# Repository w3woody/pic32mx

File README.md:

# pic32mx

This is a series of basic projects (including Eagle schematics) for the [PIC32MX270F256B](https://www.microchip.com/wwwproducts/en/PIC32mx270f256b) microcontroller, a 28-pin DIP CPU featuring 256KB of program space and 64KB of RAM. (This makes it an excellent CPU to use in place of the Atmel ATMega processors if you want to write bigger programs and use more memory.)

All these projects are built using the [MPLAB X IDE](https://www.microchip.com/mplab/mplab-x-ide) for the Macintosh, and the [MPLab PICKit 4 In-Circuit Debugger](https://www.microchip.com/Developmenttools/ProductDetails/PG164140).

## VerifyLED

The first project is a very simple one which flashes an LED. This allows you to test to make sure that you can wire up a PIC32 processor correctly and wire an LED to it, and verify your programming tools can connect correctly.

This includes the Eagle files and basic schematic for the simplest circuit necessary to run the PIC32 MPU.

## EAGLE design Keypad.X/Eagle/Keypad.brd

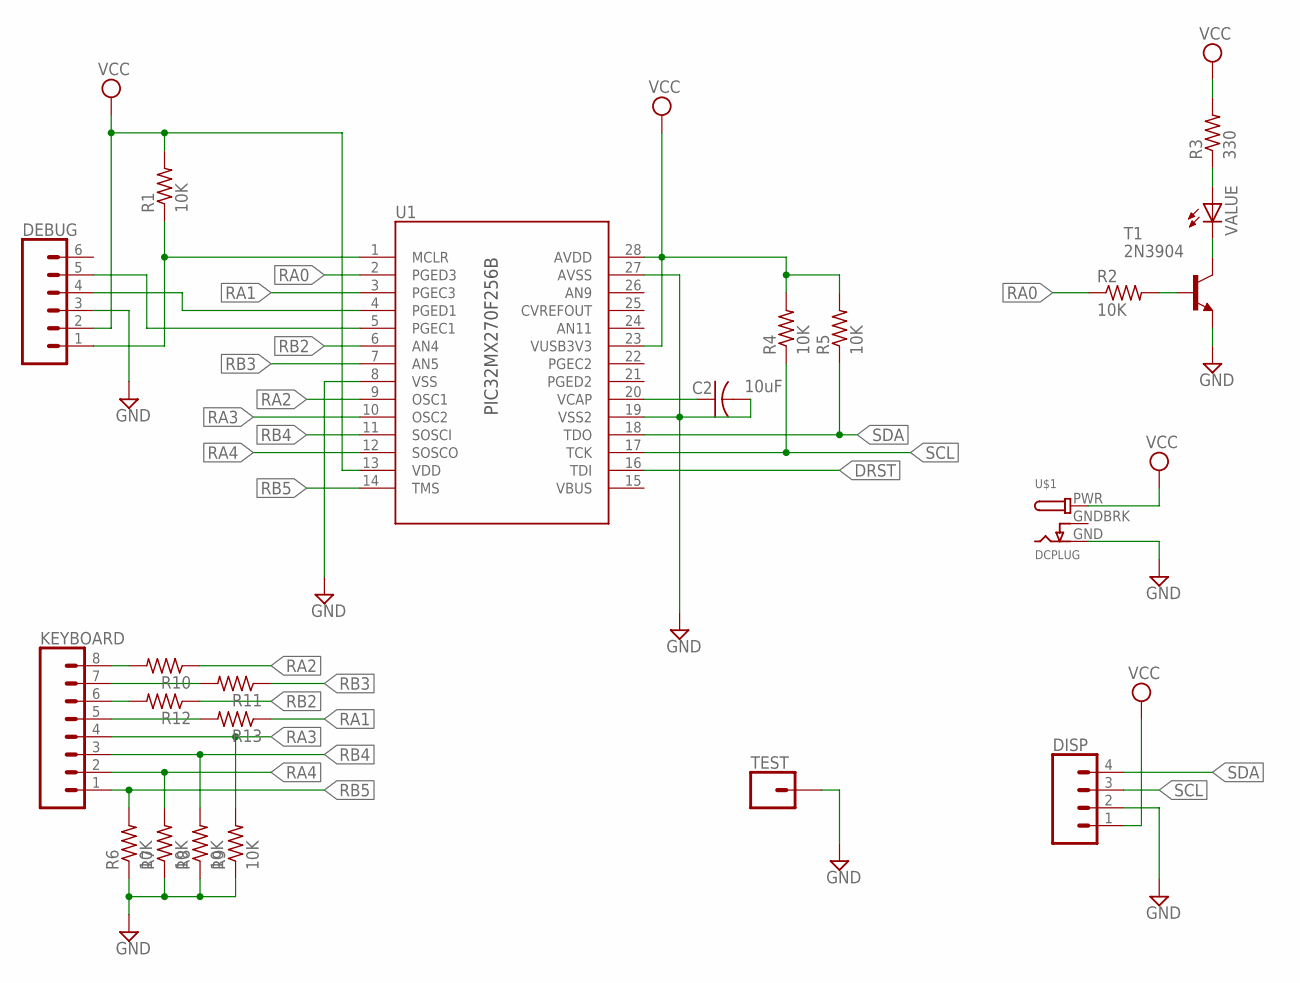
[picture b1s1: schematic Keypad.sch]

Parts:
C2: 10uF; C050-024X044
DEBUG: CONN_06LONGPADS; 1X06_LONGPADS
DISP: CONN_04; 1X04
KEYBOARD: CONN_08"; 1X08
R1, R4, R5, R6, R7, R8, R9: 10K; 0207/10
R2: 10K; 0309/10
R3, R10, R11, R12, R13: 330; 0309/10
T1: 2N3904; TO92
TEST: CONN_01; 1X01
U1: PIC32MX270F256B; DIP28
U$1: DCPLUG; POWER_JACK_SLOT
VALUE: LED5MM

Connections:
DRST: U1.16 (TDI)
GND: C2.2, DEBUG.3, DISP.2, R6.1, R7.1, R8.1, R9.1, T1.3 (E), TEST.1, U1.8 (VSS), U1.19 (VSS2), U1.27 (AVSS), U$1.GND
GNDBREAK: U$1.GNDBRK (GNDBREAK)
unnamed: DEBUG.1, R1.1, U1.1 (MCLR)
unnamed: C2.1, U1.20 (VCAP)
unnamed: KEYBOARD.8, R10.2
unnamed: DEBUG.4, U1.4 (PGED1)
unnamed: DEBUG.5, U1.5 (PGEC1)
unnamed: R2.2, T1.2 (B)
unnamed: T1.1 (C), VALUE.K (C)
unnamed: R3.1, VALUE.A
unnamed: KEYBOARD.7, R11.2
unnamed: KEYBOARD.6, R12.2
unnamed: KEYBOARD.5, R13.2
RA0: R2.1, U1.2 (PGED3)
RA1: R13.1, U1.3 (PGEC3)
RA2: R10.1, U1.9 (OSC1)
RA3: KEYBOARD.4, R9.2, U1.10 (OSC2)
RA4: KEYBOARD.2, R7.2, U1.12 (SOSCO)
RB2: R12.1, U1.6 (AN4)
RB3: R11.1, U1.7 (AN5)
RB4: KEYBOARD.3, R8.2, U1.11 (SOSCI)
RB5: KEYBOARD.1, R6.2, U1.14 (TMS)
SCL: DISP.3, R4.1, U1.17 (TCK)
SDA: DISP.4, R5.1, U1.18 (TDO)
VCC: DEBUG.2, DISP.1, R1.2, R3.2, R4.2, R5.2, U1.13 (VDD), U1.23 (VUSB3V3), U1.28 (AVDD), U$1.PWR

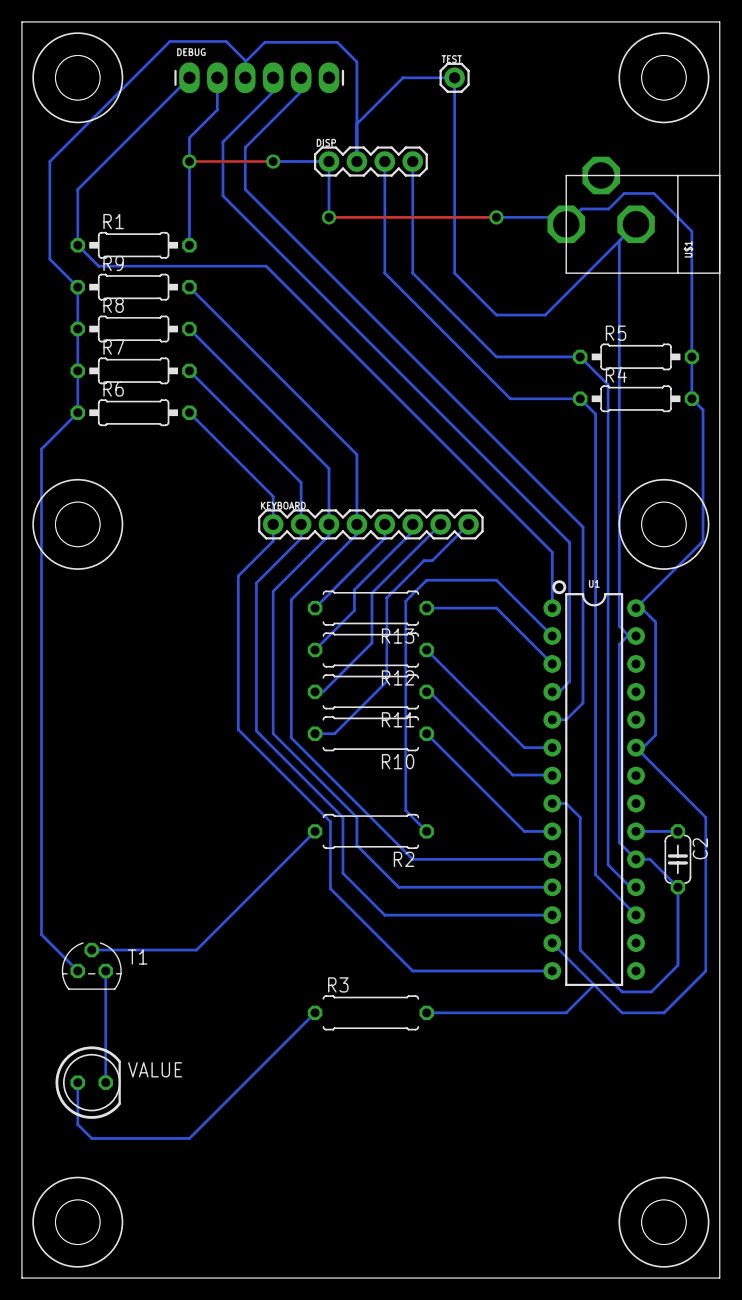
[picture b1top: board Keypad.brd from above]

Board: 2 copper layers, 63.5 x 114.3 mm, 22 parts (0 on the bottom side), 24 nets.

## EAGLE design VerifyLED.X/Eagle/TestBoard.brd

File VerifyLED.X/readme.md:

# VerifyLED

## Summary

Things shown in this project:

- The "minimal circuit" required to get a PIC32MX270F256B MPU running and talking to an in-circuit debugger for uploading software and debugging.

- Wiring up and using a digital pin for digital output, controlling an LED.

- Interrupts and interrupt vectors, and initializing a periodic timer for tracking the current time.

## Overview

This simple project tests the connection of a PIC32MX CPU (the [PIC32MX270F256B](https://www.microchip.com/wwwproducts/en/PIC32mx270f256b) CPU) to the [MPLab PICKit 4 In-Circuit Debugger](https://www.microchip.com/Developmenttools/ProductDetails/PG164140).

This consists of a very simple program which pulses a single LED on and off about once a second. This assumes the following basic circuit:

The circuit block on the left is the absolute minimum circuit (as far as I can determine) necessary to run the PIC32MX270F256B MPU. This (and the configuration code) runs the MPU at 48MHz from an internal oscillator.

I sourced the [PIC32MX270F256B MPUs from DigiKey.](https://www.digikey.com/en/products/detail/microchip-technology/PIC32MX270F256B-50I-SP/4902626) Because I tend to prototype boards rapidly, I also bought a bunch of [28 pin sockets](https://www.amazon.com/gp/product/B07GBP87RF/) because it's cheaper to toss out a failed board with a 16 cent socket than a $4.32 MPU. (Prices as of December 2020.)

The capacitor C2 must be a non-polarized ceramic capacitor; I used one from [this collection of capacitors off Amazon](https://www.amazon.com/gp/product/B07PRC5JJY/). The 10K pull-up resistor can be any 10K-ish resistors, such as one from [this set of resistors.](https://www.amazon.com/dp/B08FHLTV1M/)

(Note: I tend to blow through 10K resistors as pull-ups, so I generally buy them [in sets of 100 to 1000.](https://www.amazon.com/Projects-100EP51410K0-10k-Resistors-Pack/dp/B0185FGYQA/))

The LED and resistors are "suggested"; I generally power the whole thing at 3.3v, and any reasonable resistor from 330 ohms to 470 ohms will do the trick. I also like [these LEDs](https://www.amazon.com/gp/product/B00UWBJM0Q/); they're pretty.

I also put the LED behind a transistor in order to reduce the load on the PIC32MX MPU's pin, but you can probably skip this step and connect the LED and resistor directly to the MPU.

The plug is [one of these guys](https://www.amazon.com/gp/product/B074LK7G86/), and the Eagle board layout accepts one of these. The adapter that plugs into this plug is [one of these.](https://www.amazon.com/gp/product/B07CR2M8W6/)

----

The software itself configures the PIC32 to operate at 48MHz using the internal 8MHz oscillator. 

And this includes the files "timers.h" and "timers.c" which sets Timer 1 on the MPU as a periodic timer that drives an internal interrupt at 100 Hz. This is then used to increment an internal counter.

----

## Main.cpp

The main file shows three things.

First, it shows the list of #pragma config settings which establish basic configuration settings to get the PIC32 processor up and running. These settings establish things like the clock source, CPU clock speed, peripheral clock speed (which can be different than the CPU speed), watchdog settings and the like.

I won't dive too deeply into these settings (I don't really understand all of them myself), but the principle things to know is that these settings currently set the internal CPU clock speed to be driven from the internal oscillator (which runs at 8MHz), and using the PLL multiplier and input dividers, runs the CPU at 48MHz. (The maximum speed the CPU will run at is rated at 50MHz.)

Our internal peripheral clock speed is set at 6MHz. (This becomes important later when setting up the timer, as the timer circuit uses the peripheral clock to operate.)

The second thing it does is initialize our millisecond timer library, so we can ask for a 100 millisecond (1 second) delay. I'll discuss the library below.

The third thing it does is set up pin 2 on the 28-pin DIP as a digital output pin "RA0", sets the pin for output, then writes the value of the pin with an alternate on/off pattern on a 1 second timer. This causes our LED to flash.

The relevant segments of code are:

        ANSELAbits.ANSA0 = 0;   // digital

Our output pin is shared with an analog pin, so we must clear the ANSEL bit for port A on pin 0 in order to use the pin as a digital pin. (Notice that "RA0" is shared with "AN0" on our pin diagram in [this document.](https://ww1.microchip.com/downloads/en/DeviceDoc/PIC32MX1XX2XX%20283644-PIN_Datasheet_DS60001168L.pdf))

        TRISAbits.TRISA0 = 0;   // output

This sets the digital pin to output.

Then we manipulate the pin itself using the LATA latch registers:

        LATAbits.LATA0 = 1; // On

This turns our LED on, and

        LATAbits.LATA0 = 0; // Off

turns off our LED.

## Timer.c/Timer.h

Our timer library sets up timer 1 as a periodic interrupt generator which triggers an interrupt every 1/100th of a second. This shows two features: setting up Timer 1, and setting it up to fire an interrupt in multi-vector interrupt mode.

Discussions for interrupts can be found [here](https://ww1.microchip.com/downloads/en/DeviceDoc/60001108H.pdf), and for the timers [here](https://ww1.microchip.com/downloads/en/DeviceDoc/61105F.pdf).

Note that the interrupt declaration itself is documented in the [XC32 C/C++ Compiler User's Guide](https://ww1.microchip.com/downloads/en/DeviceDoc/50001686J.pdf) at Chapter 14: Interrupts. This both includes the format of the `__ISR` compiler directive, as well as the various `__builtin` functions which handle interrupts.

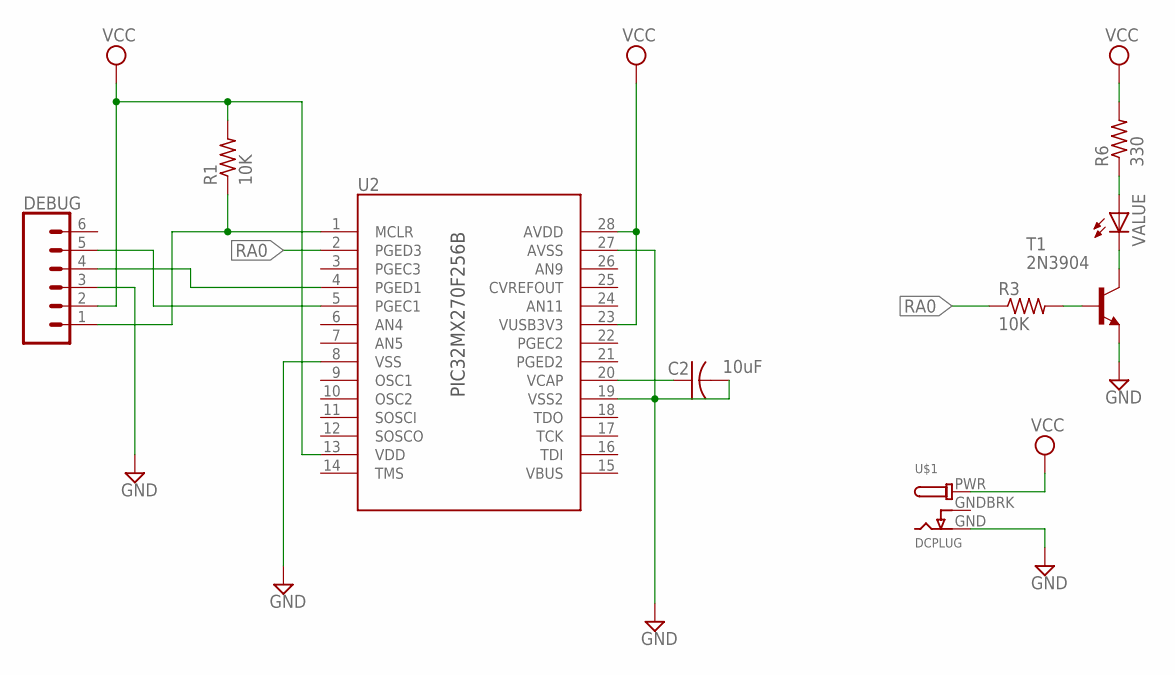
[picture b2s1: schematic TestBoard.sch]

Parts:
C2: 10uF; C050-024X044
DEBUG: CONN_06LONGPADS; 1X06_LONGPADS
R1: 10K; 0207/10
R3: 10K; 0309/10
R6: 330; 0309/10
T1: 2N3904; TO92
U2: PIC32MX270F256B; DIP28
U$1: DCPLUG; POWER_JACK_SLOT
VALUE: LED5MM

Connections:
GND: C2.2, DEBUG.3, T1.3 (E), U2.8 (VSS), U2.19 (VSS2), U2.27 (AVSS), U$1.GND
GNDBREAK: U$1.GNDBRK (GNDBREAK)
unnamed: DEBUG.1, R1.1, U2.1 (MCLR)
unnamed: C2.1, U2.20 (VCAP)
unnamed: DEBUG.4, U2.4 (PGED1)
unnamed: DEBUG.5, U2.5 (PGEC1)
unnamed: R3.2, T1.2 (B)
unnamed: T1.1 (C), VALUE.K (C)
unnamed: R6.1, VALUE.A
RA0: R3.1, U2.2 (PGED3)
VCC: DEBUG.2, R1.2, R6.2, U2.13 (VDD), U2.23 (VUSB3V3), U2.28 (AVDD), U$1.PWR

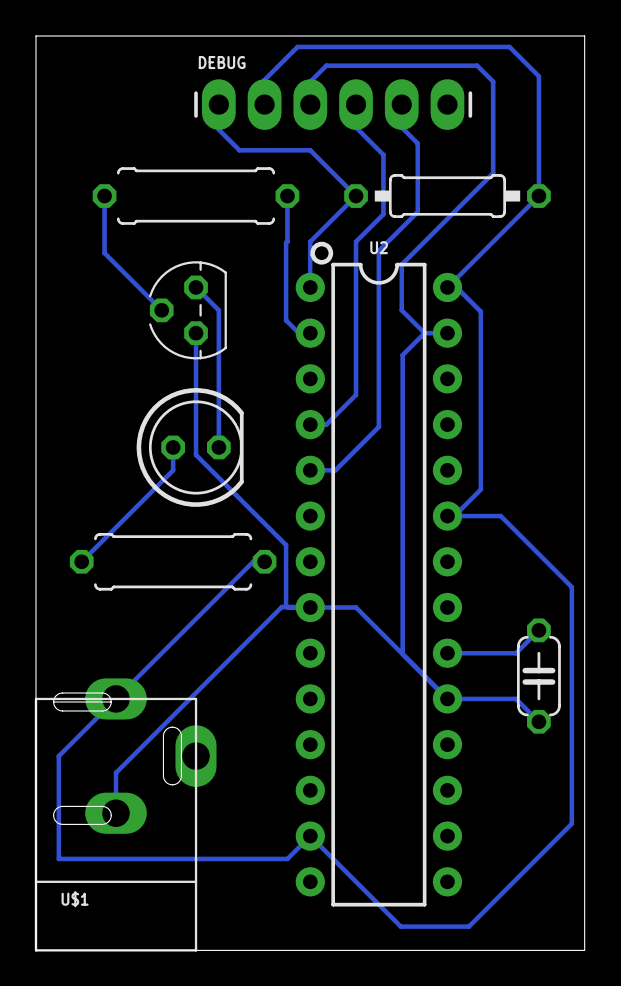
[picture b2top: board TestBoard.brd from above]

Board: 2 copper layers, 30.5 x 50.8 mm, 9 parts (0 on the bottom side), 10 nets.

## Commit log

2020-12-14 Initial check-in; VerifyLED
2020-12-14 Minor updates
2020-12-14 Update ignore.
2020-12-14 Update readme to expand on what is in the VerifyLED code
2020-12-22 Initial check-in of SSD1306 project.
    This is the initial check-in of the SSD1306 project. It still needs documentation and some of the routines still need work, but it's complete enough to give a reasonable example of controlling cheap 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
    This also includes a simple I2C two-wire implementation that uses interrupts, as well as a basic graphics display class that controls an SSD1306-based 128x64 display, along with the circuit board lay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
2020-12-30 Update SSD code
2020-12-30 Keypad schematic, keypad code.

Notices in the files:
parts and their libraries:
SparkFun-Connectors: Licensing: Creative Commons ShareAlike 4.0 International - https://creativecommons.org/licenses/by-sa/4.0
